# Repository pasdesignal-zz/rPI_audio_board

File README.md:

rPI_audio_board
===============
best current version to build is v0.8 (updated Oct 2013)
-------------------------------------
a soundcard for the raspberry pi

This is a developing extension board for the raspberry pi model rev.B

It is largely untested as yet, and there are no guarantees or liability. Use these files at your own risk.

It is intended for use with aSOC i2s audio drivers and requires a kernel build, which you can read more about at my blog or on the raspberry pi forums.

This is also an experiment with using github for hardware file sharing and revision control. I hope others will join me developing this hardware as an opensource project and work with github to facilitate the collabortation. 

If you are interested in purchasing a ready made board, they will be available soon via Tindie.

The schematic design and layout was done using KiCad http://kicad.sourceforge.net, a Free Software EDA tool for Linux, Windows and Mac OS. (But it works best in Windows) You will need KiCad to open the .sch or .brd files - gEDA or Eagle will not work.

pasdesignal

http://www.noiseisgood.co.nz

Oct 2013

License: All designs are released under 

Creative Commons NonCommercial-ShareAlike 

CC BY-NC-SA

Please contact me for commercial opportunities. 

Need a great library for Kicad?
Heres a great place to get recent builds and an awesome library which I use in this project:
http://www.escalalibre.com/edwt/

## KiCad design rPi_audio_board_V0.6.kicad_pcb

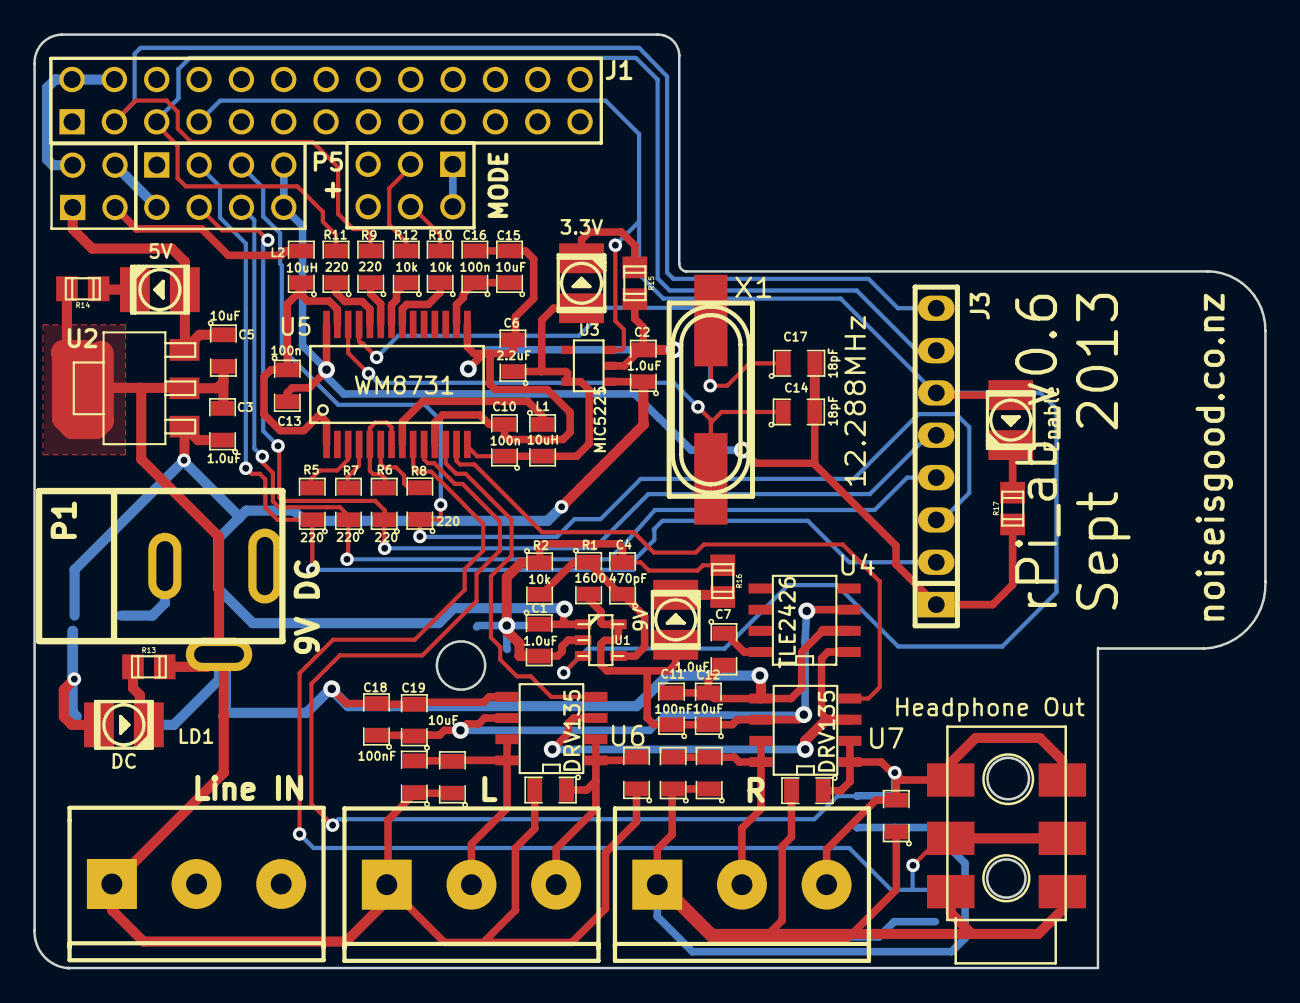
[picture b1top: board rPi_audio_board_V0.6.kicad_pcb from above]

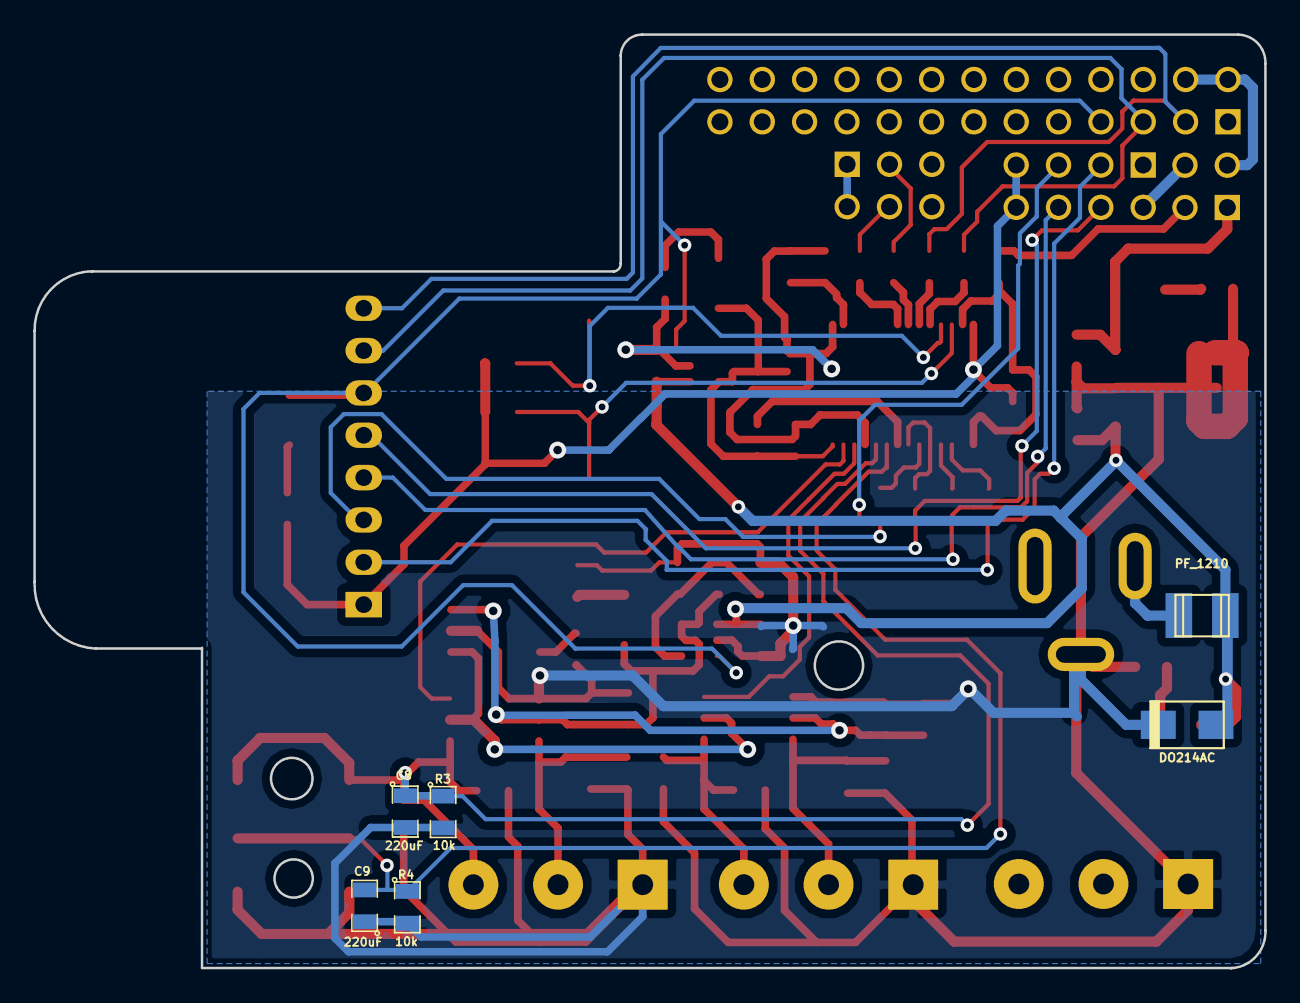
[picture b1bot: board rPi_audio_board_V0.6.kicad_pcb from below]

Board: 2 copper layers, 73.9 x 56.0 mm, 60 parts (6 on the bottom side), 52 nets.

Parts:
3.3V, 5V, 9V: Led_PLCC2_3528
C1, C2, C3, C7: 1.0uF; SM0805
C4: 470pF; SM0805
C5, C12, C15, C19: 10uF; SM0805
C6: 2.2uF; SM0805
C8, C9: 220uF; SM0805
C10, C13, C16: 100n; SM0805
C11, C18: 100nF; SM0805
C14, C17: 18pF; SM0805
DO214AC: D***; do214ac
Enable: Led_PLCC2_3528
J1: pin_array_13x2
J3: PIN OUT; pin_strip_8
L: mors_3p
L1, L2: 10uH; SM0805
LD1: DC; Led_PLCC2_3528
Line IN: mors_3p
P1: 9V DC; dc_socket
P5: pin_array_3x2
PF_1210: Polyfuse; r_1210
R: mors_3p
R1: 1600; SM0805
R2, R3, R4, R10, R12: 10k; SM0805
R5, R6, R7, R8, R9, R11: 220; SM0805
R13: 3k6; r_0805
R14, R15, R16, R17: 750; r_0805
U1: MIC5207BM5; sot23-5
U2: MIC39100-5.0; sot223
U3: MIC5225; SOT23-5
U4: TLE2426; SO8E
U5: WM8731; ssop-28
U6, U7: DRV135; SO8E
X1: 12.288MHz; crystal_hc-49/smd

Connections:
+3.3VDC: 3.3V.1, C6.1, L1.1, U3.5, U5.8
+9VDC: C11.1, C12.1, C18.1, C19.1, R1.2, U1.5, U4.3, U6.6, U7.6
AGND: C10.2, C11.2, C12.2, C15.2, C16.2, C18.2, C19.2, L.1, Line IN.1, R.1, R3.2, R4.2, U5.11, U5.15, U6.5, U7.5
DC IN: C1.1, C2.1, C3.1, U1.1, U2.1, U3.1
DGND: C13.2, C14.2, C17.2, J1.6, J1.9, J1.14, J1.20, J1.25, J3.1, P5.1, P5.2, R17.2, U5.28
DVDD: P5.5, P5.6
GNDPWR: 9V.2, C1.2, C2.2, C3.2, C4.2, C5.2, C6.2, C7.2, P1.1, R2.1, R13.1, R14.1, R15.1, U1.2, U2.2, U3.2, U4.2
GPIO4: Enable.1, J1.7, J3.6, U1.3, U3.3
I2C_CLK: J1.5, J3.7, R11.2
I2C_SDA: J1.3, J3.8, R9.2
LHPOUT: C9.1, U5.9
LOUT: U5.12, U6.4
unnamed: P5.3, R12.2
unnamed: C4.1, R1.1, R2.2, U1.4
unnamed: R12.1, U5.22
unnamed: P5.4, R10.2
unnamed: R5.2, U5.3
unnamed: C13.1, L2.1, U5.1, U5.27
unnamed: R8.2, U5.6
unnamed: R7.2, U5.4
unnamed: C7.1, U4.8
unnamed: R9.1, U5.23
unnamed: L.3, Line IN.3
unnamed: R10.1, U5.21
unnamed: LD1.2, R13.2
unnamed: 9V.1, R16.1
unnamed: Enable.2, R17.1
unnamed: 3.3V.2, R.2, R15.2
unnamed: 5V.2, R14.2
unnamed: P1.2, R.3
unnamed: J1.2, J1.4
unnamed: 5V.1, C5.1, U2.3
unnamed: U6.7, U6.8
unnamed: C8.2, R3.1
unnamed: C9.2, R4.1
unnamed: C15.1, C16.1, U5.16
unnamed: C14.1, U5.26, X1.1
unnamed: C17.1, U5.25, X1.2
unnamed: U6.1, U6.2
unnamed: R11.1, U5.24
unnamed: L.2, Line IN.2, U5.17
unnamed: C10.1, L1.2, U5.14
unnamed: R6.2, U5.5, U5.7
unnamed: U7.1, U7.2
unnamed: U7.7, U7.8
PCM_CLK: J3.2, R5.1
PCM_DIN: J3.3, R8.1
PCM_DOUT: J3.4, R7.1
PCM_FS: J3.5, R6.1
RHPOUT: C8.1, U5.10
ROUT: U5.13, U7.4
VREF: U4.1, U6.3, U7.3

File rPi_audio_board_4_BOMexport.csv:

"Id";"Designator";"Package";"Quantity";"Designation";"Supplier and ref";
1;"Left,Right";"mors_3p";2;"";;;
2;"J2";"pin_array_4x2reversed";1;"";;;
3;"J1";"pin_array_13x2";1;"";;;
4;"C1,C2,C3,C7";"SM0805";4;"1.0uF";;;
5;"C4";"SM0805";1;"470pF";;;
6;"C5,C12,C15,C19";"SM0805";4;"10uF";;;
7;"C6";"SM0805";1;"2.2uF";;;
8;"C8,C9";"SM0805";2;"220uF";;;
9;"C10,C13,C16";"SM0805";3;"100n";;;
10;"C11,C18";"SM0805";2;"100nF";;;
11;"C14,C17";"SM0805";2;"18pF";;;
12;"L1,L2";"SM0805";2;"10uH";;;
13;"DC IN";"dc_socket";1;"9V DC";;;
14;"";"mors_3p";1;"Headphone Out";;;
15;"P4";"mors_3p";1;"Line In";;;
16;"P5";"pin_array_3x2";1;"MODE SET";;;
17;"R1";"SM0805";1;"1600";;;
18;"R2,R3,R4,R10,R12";"SM0805";5;"10k";;;
19;"R5,R6,R7,R8,R9,R11";"SM0805";6;"220";;;
20;"U1";"sot23-5";1;"MIC5207BM5";;;
21;"U2";"sot223";1;"MIC39100-5.0";;;
22;"U3";"SOT23-5";1;"";;;
23;"U4";"SO8E";1;"";;;
24;"U5";"ssop-28";1;"";;;
25;"U6,U7";"SO8E";2;"DRV135";;;
26;"X1";"crystal_hc-49/smd";1;"12.288MHz";;;
27;",,,,,,,";"SM0805";8;"";;;

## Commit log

2013-08-11 Rename rpi_audio_board_v0.4 to rpi_audio_board_v04.sch
2013-08-11 upload
2013-08-11 uploaded
2013-08-11 shcematic update
2013-08-11 schematic development
2013-08-11 Found GPIO header layout file
2013-08-11 board layout changes
    second header added, flipped and put onto top side.
2013-08-11 started on rough board layout
2013-08-12 library rearrange
2013-08-12 board development, tidy up gnd etc
2013-08-22 refined folder for size
2013-08-22 better file labelling
2013-08-22 3d render of board
2013-08-22 3d render
2013-08-22 3d render better
2013-08-22 autosave
2013-08-22 better 3d model
2013-08-22 readme edited with untested clause
2013-08-25 schematic pdf
2013-10-07 board revised design
2013-10-07 deleted obsolete versions
2013-10-17 started v0.9 pcb layout
